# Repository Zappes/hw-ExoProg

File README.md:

Programmer breakout board for ATtiny85
======================================

What Is this?
-------------
When I use an ATtiny85 instead of an ATmega328, I do so because I want to save space on the PCB. This normally means that I omit the ISP header which makes working on the software a little tricky - I have to do all the programming on a breadboard or I have to remove the chip from the PCB, program it using an external programmer and then re-insert it into the circuit. Quite a pain, actually.

The ExoProg is a little board that contains an ATtiny85 and two 4:2 multiplexer ICs. There also is a second 8-pin socket which is connected using a simple cable to the socket in the actual circuit. The last connector is an ISP header to which a programmer can be connected. Normally, the pins of the microcontroller are simply connected to the pins of the second socket, so the ExoProg doesn't really do anything - it's just like an ATtiny85 on a wire.

![The PCB for the ExoProg][1]

As soon as the reset pin of the ATtiny is pulled low, though, the multiplexers cut the connection between the ISP pins of the ATtiny and the external circuit and connect the microcontroller's ISP pinbs to the programmer header. This makes it possible to program the ATtiny without interfering with the actual circuit at all - the multiplexers make sure that the ISP signals are completely isolated from the external circuit.

![The ExoProg assembled, connected and ready for action][2]

A very important aspect is that there is no Vcc connection between the ExoProg and the actual circuit, only GND is connected through the adapter cable. This really saves a lot of headache in situations where you have a circuit running at a voltage lower than 5V and a programmer that uses 5V - that voltage will *never* reach your circuit and destroy it during the programming cycle.

I made a little video when I actually built the device. I guess that is quite helpful, but it's in German: http://youtu.be/9HViv_5PDsI

  [1]: https://raw.githubusercontent.com/Zappes/hw-ExoProg/master/Images/ExoProg-PCB_small.jpg
  [2]: https://raw.githubusercontent.com/Zappes/hw-ExoProg/master/Images/ExoProg-Setup-small.jpg

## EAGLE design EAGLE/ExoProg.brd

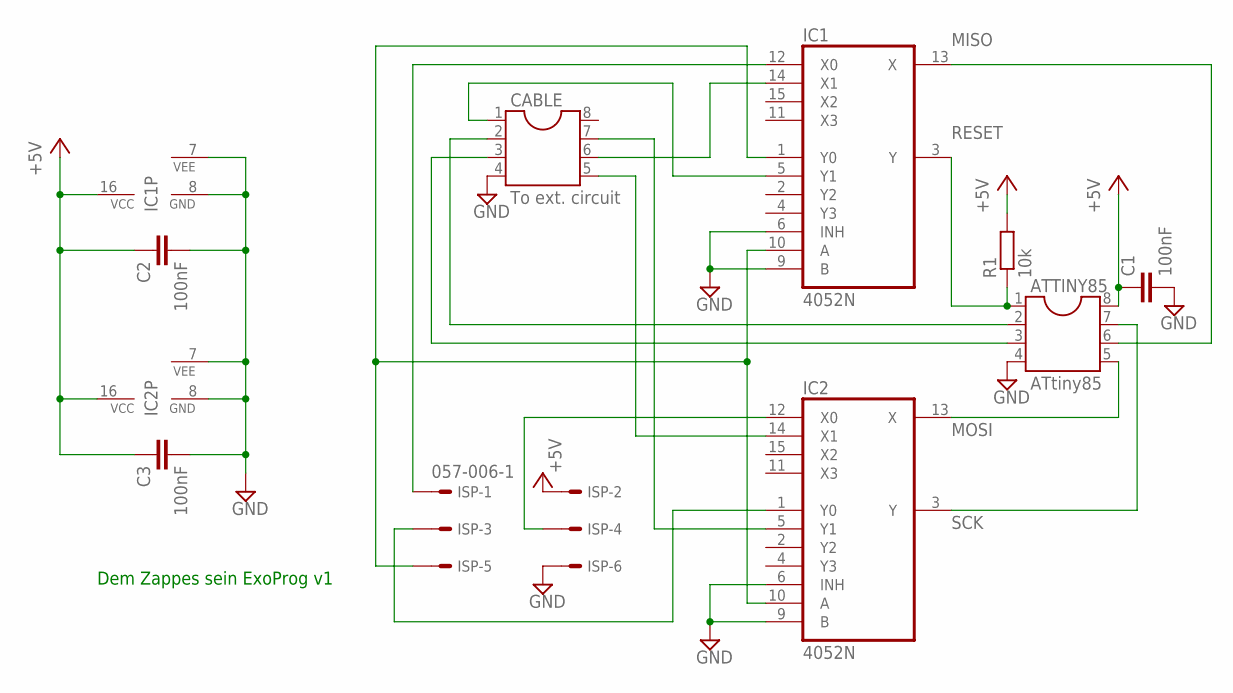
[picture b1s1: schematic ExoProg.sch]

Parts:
ATTINY85: ATtiny85; DIL08
C1, C2, C3: 100nF; C2.5-3
CABLE: To ext. circuit; DIL08
IC1, IC2: 4052N; DIL16
ISP: 057-006-1
R1: 10k; 0207/10

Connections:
+5V: ATTINY85.8, C1.1, C2.1, C3.1, IC1.16 (VCC), IC2.16 (VCC), ISP.2, R1.2
C_MISO: CABLE.6, IC1.14 (X1)
C_MOSI: CABLE.5, IC2.14 (X1)
C_RESET: CABLE.1, IC1.5 (Y1)
C_SCK: CABLE.7, IC2.5 (Y1)
GND: ATTINY85.4, C1.2, C2.2, C3.2, CABLE.4, IC1.6 (INH), IC1.7 (VEE), IC1.8 (GND), IC1.9 (B), IC2.6 (INH), IC2.7 (VEE), IC2.8 (GND), IC2.9 (B), ISP.6
I_MISO: IC1.12 (X0), ISP.1
I_MOSI: IC2.12 (X0), ISP.4
I_RESET: IC1.1 (Y0), IC1.10 (A), IC2.10 (A), ISP.5
I_SCK: IC2.1 (Y0), ISP.3
MISO: ATTINY85.6, IC1.13 (X)
MOSI: ATTINY85.5, IC2.13 (X)
PIN2: ATTINY85.2, CABLE.2
PIN3: ATTINY85.3, CABLE.3
RESET: ATTINY85.1, IC1.3 (Y), R1.1
SCK: ATTINY85.7, IC2.3 (Y)

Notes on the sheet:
Dem Zappes sein ExoProg v1

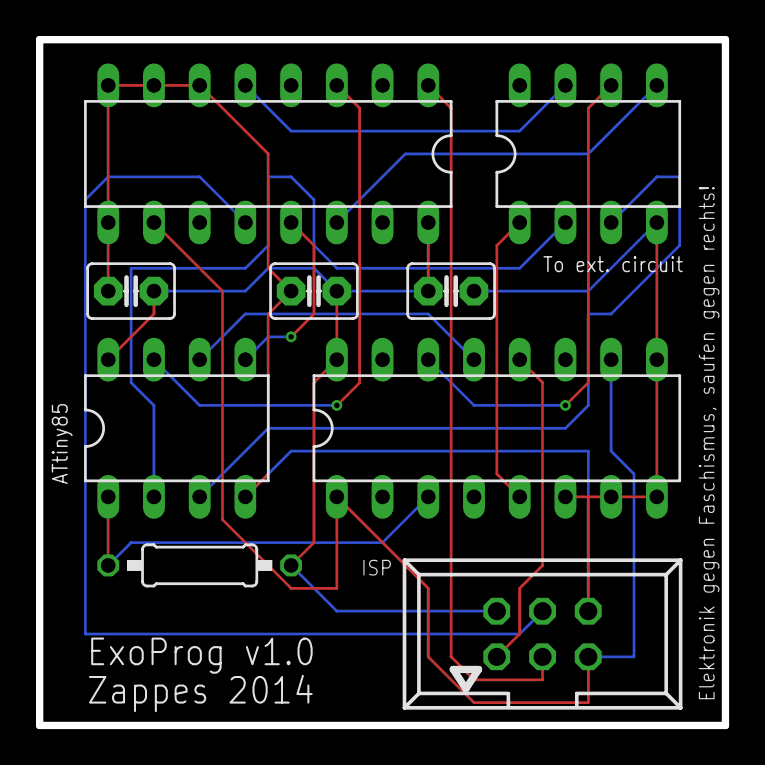
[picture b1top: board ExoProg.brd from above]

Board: 4 copper layers, 38.1 x 38.1 mm, 9 parts (0 on the bottom side), 16 nets.

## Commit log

2014-07-17 Commit des fertigen Projekts
2014-07-17 Crap gelöscht
2014-07-17 added README
2014-07-18 Added images of the PCB
2014-07-18 Updated the README, added pictures
2014-07-18 Fixed a typo
